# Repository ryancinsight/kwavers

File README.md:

# Kwavers 🌀

**An interdisciplinary ultrasound-light physics simulation library.** Kwavers models acoustic wave propagation, cavitation dynamics, and sonoluminescence for multi-modal imaging research and physics studies.

## 📋 Library Components

### Physics Models
- **Acoustic Wave Propagation**: Linear and nonlinear wave equations
- **Cavitation Dynamics**: Bubble physics implementations
- **Multi-Physics Coupling**: Basic acoustic-thermal interactions
- **Electromagnetic Models**: Wave propagation in various media

### Numerical Methods
- **FDTD Solver**: Finite difference time domain implementation
- **PSTD Solver**: Pseudospectral time domain method
- **PINN Support**: Physics-informed neural networks (experimental)
- **Boundary Conditions**: Various absorbing and reflecting boundaries

### Application Areas
- **Research Simulations**: Acoustic wave propagation studies
- **Imaging Algorithms**: Basic beamforming and reconstruction
- **Material Modeling**: Acoustic properties of different media
- **Signal Processing**: Filtering and analysis utilities

## 📊 Current Development Status

**Recently completed:** the workspace crate split (ADR-011) — the ~460k-LOC
`kwavers` monolith is decomposed into per-layer crates to cut incremental build
times. There is **no facade**: consumers (including the Python bindings) depend on
the layer crates directly (`kwavers_core`, `kwavers_grid`, `kwavers_solver`, …).
The `kwavers` crate is now only a thin top-level **app/integration** crate — it
hosts the binary and the cross-cutting tests/examples/benches, and re-exports
nothing.

### Workspace layout

| Crate | Layer / responsibility |
|-------|------------------------|
| [`kwavers-core`](crates/kwavers-core) | Constants, error types, arena allocation, time/logging utilities |
| [`kwavers-math`](crates/kwavers-math) | FFT, linear algebra, numerics, geometry, statistics, SIMD |
| [`kwavers-grid`](crates/kwavers-grid) | Cartesian/cylindrical grids, coordinates, topology, operators, geometric domains |
| [`kwavers-field`](crates/kwavers-field) | Field component indices (SSOT), field-type mapping, operations, statistics |
| [`kwavers-signal`](crates/kwavers-signal) | Waveforms, pulses, sweeps, modulation, windowing, filters |
| [`kwavers-medium`](crates/kwavers-medium) | Homogeneous/heterogeneous media, acoustic/elastic/optical/thermal properties |
| [`kwavers-phantom`](crates/kwavers-phantom) | Clinical tissue-phantom builders and Shepp-Logan references |
| [`kwavers-mesh`](crates/kwavers-mesh) | Tetrahedral FEM meshes, quality metrics, gaia bridge |
| [`kwavers-boundary`](crates/kwavers-boundary) | CPML/PML absorbing layers, FEM/BEM boundaries, coupling, periodic |
| [`kwavers-source`](crates/kwavers-source) | `Source` trait, grid/mask sources, wavefronts, apodization |
| [`kwavers-receiver`](crates/kwavers-receiver) | Sensor-array geometry (SSOT), recorders, point sensors, grid sampling |
| [`kwavers-transducer`](crates/kwavers-transducer) | Bowls, phased/linear/matrix/hemispherical arrays, beamforming, PAM, ultrafast |
| [`kwavers-imaging`](crates/kwavers-imaging) | DICOM/CT/NIfTI loaders, ultrasound/photoacoustic models, CEUS, fusion |
| [`kwavers-physics`](crates/kwavers-physics) | Nonlinear acoustics, bubble dynamics, thermal, optics, chemistry, elastic waves |
| [`kwavers-solver`](crates/kwavers-solver) | FDTD / PSTD / k-space / Helmholtz, BEM, FWI / RTM / CBS, PINN |
| [`kwavers-gpu`](crates/kwavers-gpu) | Hephaestus-backed provider-generic GPU backend; concrete `ComputeBackend` impls |
| [`kwavers-simulation`](crates/kwavers-simulation) | Builders, runners, multi-physics coupling, modality pipelines, backends |
| [`kwavers-analysis`](crates/kwavers-analysis) | Signal processing, conservation, validation, ML/uncertainty, plotting |
| [`kwavers-diagnostics`](crates/kwavers-diagnostics) | Reconstruction, multi-modal fusion, Doppler, spectroscopy, decision support |
| [`kwavers-therapy`](crates/kwavers-therapy) | HIFU / histotripsy / lithotripsy planning, theranostic guidance, dose & safety |
| [`kwavers-driver`](crates/kwavers-driver) | Physics-guided, manufacturing-aware driver-electronics (PCB) design |
| [`kwavers`](crates/kwavers) | Thin top-level app/integration crate: binary + cross-cutting tests/examples/benches (no re-exports) |
| [`kwavers-python`](crates/kwavers-python) | PyO3 bindings (`pykwavers`); depends on the layer crates directly; no domain logic |

Tyche owns reproducible counter streams, Latin-hypercube and Sobol designs,
online moments, correlation screening, and finite-sample conformal
calibration. Kwavers owns physical-domain transforms, model execution, Leto
array presentation, and domain-specific score definitions. Geometry maps
Tyche designs directly into validated rectangles, disks, and balls through one
single-allocation collector; Analysis and PINN fixed-design code carry no
independent provider algorithms, while model-residual adaptive refinement
remains solver-owned. See
[ADR 043](docs/ADR/043-tyche-uncertainty-provider.md).

Layer crates are at `3.0.0`; the completed split targets `4.0.0` (see
[RELEASE_v4.0.0 notes in CHANGELOG](CHANGELOG.md)). `kwavers-python` is `0.1.0`.

Validation status: the k-space pseudospectral solver matches the k-Wave
reference solver on the homogeneous-water IVP benchmark at Pearson
r = 1.000000000 (2-D) and r = 0.999999994 (3-D). The comparison is a Rust test in
the default gate against reference fields committed to this repository — see
[Reference Benchmark Coverage](#reference-benchmark-coverage).

### Python Releases

GitHub Releases tagged `kwavers-python-v<version>` build one locked
Python-3.8-compatible stable-ABI wheel per operating system for Linux, Windows,
and macOS. The workflow installs and imports each wheel as `pykwavers`, verifies
the `kwavers-python` distribution identity and Cargo-owned version, attests and
attaches the exact artifacts, then publishes that same wheel set to PyPI
through OIDC Trusted Publishing.

### Rust Crate Releases

The 23 reusable Rust packages publish to crates.io in local dependency order.
The `Crates.io Release` workflow validates a named workspace package on manual
dispatch. After its required first release is bootstrapped and its crates.io
Trusted Publisher is registered, a GitHub Release tagged
`crate-<package>-v<version>` packages, verifies, and publishes the matching
Cargo version with a short-lived OIDC token. Validation runs in a separate
read-only job. The publish job is bound to the GitHub `crates-io` environment.
The PyO3 and `xtask` packages are explicitly non-publishable; all Rust library
releases use their package names.

Detailed history lives in [`CHANGELOG.md`](CHANGELOG.md); current work and gaps
are tracked in [`backlog.md`](backlog.md), [`CHECKLIST.md`](CHECKLIST.md), and
[`gap_audit.md`](gap_audit.md).

### Architecture Overview

Kwavers follows a layered architecture designed for scientific computing:

```
Therapy / Diagnostics → Clinical planning, theranostic guidance, dose & safety
Simulation Layer      → Multi-physics orchestration, modality pipelines
Analysis Layer        → Signal processing, beamforming, imaging algorithms
Solver Layer          → Numerical methods (FDTD, PSTD, k-space, FWI, PINN)
Physics Layer         → Wave equations, bubble dynamics, constitutive relations
Domain Layer          → Problem geometry, materials, sources, sensors
Math Layer            → Linear algebra, FFT, numerical primitives
Core Layer            → Fundamental types, error handling
```

The module DAG is acyclic and linear (`core → math → domain → physics → solver →
analysis → simulation → diagnostics/therapy`); each layer is now its own crate.

Cross-repository foundations remain below that DAG. Public
[Asclepius](https://github.com/ryancinsight/asclepius) owns CEM43, Arrhenius
thermal damage, and independent-insult composition. Kwavers converts stored
temperatures to Aequitas quantities at its boundaries and retains spatial
fields, tissue presets, clinical thresholds, and an independent validation
oracle. See [ADR 044](docs/ADR/044-asclepius-response-ownership.md).

Public [Hyperion](https://github.com/ryancinsight/hyperion) owns photon and
optical interaction coefficients, reduced scattering, optical depth,
Beer-Lambert transmission, and the diffusion-derived coefficient laws.
`kwavers-medium` retains tissue identity, refractive index, presets, and maps;
`kwavers-physics` and `kwavers-solver` retain spatial transport algorithms and
photoacoustic coupling. This boundary removes the former `kwavers-optics`
formula module plus the parallel `DiffusionOpticalProperties` and
`OpticalAbsorption` models instead of adding a facade around them. See
[ADR 046](docs/ADR/046-hyperion-optical-transport-ownership.md).

Key architectural decisions:
- **Layer Separation**: Unidirectional dependencies prevent circular imports
- **Domain Purity**: Core entities remain free of application logic
- **Trait-Based Design**: Physics specifications defined as traits for testability
- **Feature Flags**: Optional components (GPU, PINN, API) can be enabled as needed

## 🚀 Quick Start

### Installation

Add the layer crates you need to your `Cargo.toml`:

```toml
[dependencies]
kwavers-grid = "3.0.0"
kwavers-medium = "4.0.0"
```

For GPU acceleration and advanced features, add the top-level integration crate:

```toml
[dependencies]
kwavers = { version = "3.0.0", features = ["gpu", "pinn"] }
```

### Example 1: Basic Grid Setup

```rust
use kwavers_grid::Grid;

fn main() -> Result<(), Box<dyn std::error::Error>> {
    // Create a 3D computational grid
    let grid = Grid::new(100, 100, 100, 0.001, 0.001, 0.001)?;
    println!("Created grid: {}×{}×{} points", grid.nx, grid.ny, grid.nz);
    println!("Grid spacing: {} m", grid.dx);
    Ok(())
}
```

### Example 2: Material Properties

```rust
use kwavers_grid::Grid;
use kwavers_medium::HomogeneousMedium;

fn main() -> Result<(), Box<dyn std::error::Error>> {
    // Create a computational grid
    let grid = Grid::new(100, 100, 100, 0.001, 0.001, 0.001)?;

    // Define acoustic properties for water
    let density = 1000.0;      // kg/m³
    let sound_speed = 1500.0;  // m/s
    let mu_a = 0.0;            // optical absorption coefficient (1/m)
    let mu_s_prime = 0.0;      // reduced optical scattering coefficient (1/m)

    // Create a homogeneous water medium
    let medium = HomogeneousMedium::new(
        density,
        sound_speed,
        mu_a,
        mu_s_prime,
        &grid,
    );

    println!("Water properties:");
    println!("  Density: {} kg/m³", density);
    println!("  Sound speed: {} m/s", sound_speed);
    println!("  Acoustic impedance: {} MPa·s/m", density * sound_speed / 1e6);

    Ok(())
}
```

### Example 3: Basic Acoustic Calculations

```rust
// Basic acoustic property calculations
fn main() {
    // Acoustic impedance calculation: Z = ρc
    let density_water = 1000.0;     // kg/m³
    let speed_water = 1500.0;       // m/s
    let impedance_water = density_water * speed_water; // Pa·s/m

    println!("Water acoustic impedance: {:.0} Pa·s/m", impedance_water);

    // Reflection coefficient: R = (Z2 - Z1)/(Z2 + Z1)
    let density_air = 1.2;          // kg/m³
    let speed_air = 343.0;          // m/s
    let impedance_air = density_air * speed_air;

    let reflection_coeff = (impedance_air - impedance_water) /
                          (impedance_air + impedance_water);

    println!("Air-water reflection coefficient: {:.4}", reflection_coeff);
}
```

## 📚 Documentation

### 📖 Documentation

- **[Published Kwavers book](https://ryancinsight.github.io/kwavers/)** - Hosted mdBook site
- **[API Reference](https://docs.rs/kwavers)** - Generated Rust documentation
- **[Examples](examples/)** - Basic usage examples
- **[The Kwavers book](docs/book/)** - Chapters, figures, validation narratives
- **[Architecture Decision Records](docs/ADR/)** - Design decisions (incl. ADR-011 crate split)
- **[Documentation index](docs/README.md)** - What lives under `docs/`

### 🎯 Basic Usage

See the `examples/` directory for basic usage patterns:

```bash
# List available examples
cargo run --example

# Run a basic example (if available)
cargo run --example basic_simulation
```

**Basic Test**: Check compilation
```bash
cargo check
```

### 🏗️ Architecture

Kwavers is structured with layered separation intended to support scientific computing workflows:

```
Clinical Applications    → Research use cases, safety monitoring
Analysis & Imaging       → Signal processing, reconstruction algorithms
Simulation Orchestration → Multi-physics coupling, time integration
Numerical Solvers        → FDTD, PSTD, PINN, spectral methods
Physics Specifications   → Wave equations, constitutive relations
Problem Domain           → Geometry, materials, boundary conditions
Mathematical Primitives  → Linear algebra, FFT, interpolation
Core Infrastructure      → Error handling, memory management
```

The architecture aims to separate concerns while maintaining flexibility for different research applications. Layer boundaries help organize code but are not strictly enforced in all areas during active development.

## 🤝 Contributing

This is an active research project under development. Contributions are welcome! The codebase follows strict quality standards and clean architecture principles.

### 📝 Development Philosophy

- **Clean Codebase**: No dead code, deprecated code, or build artifacts
- **Deep Vertical Hierarchy**: Modules organized by domain with clear separation of concerns
- **Single Source of Truth**: Shared accessors, no duplication
- **Zero Technical Debt**: All TODOs resolved with full implementation or removed
- **Architectural Purity**: Unidirectional dependencies, no circular imports

### 🚀 Getting Started

1. **Check Status**: Review [`CHECKLIST.md`](CHECKLIST.md) for current task status
2. **Review Plans**: See [`backlog.md`](backlog.md) for planned work and [`gap_audit.md`](gap_audit.md) for known gaps
3. **Build a crate**: `cargo check -p kwavers-core` (per-crate checks are fast post-split)
4. **Run Tests**: `cargo nextest run -p <crate>`; use
   `cargo test-gpu-consumers` when changing the shared GPU simulation/Python
   dependency graph, so Cargo compiles their common graph once; use
   `cargo test -p <crate> --doc` for doctests
5. **Read Docs**: [`docs/book/`](docs/book/) for narratives, [`docs/ADR/`](docs/ADR/) for design decisions
6. **Install the hooks**: `git config core.hooksPath .githooks`

   Git never applies tracked hooks on its own, so this is a one-time step per
   clone. The `pre-push` hook runs `scripts/lockfile.py --check`, which is the
   same check CI runs. It matters most when working inside the Atlas stack: the
   stack's `[patch]` overlay makes cargo resolve first-party dependencies to
   local paths and write a `Cargo.lock` with every `source = "git+..."` line
   stripped. That lock resolves fine under the overlay and fails every
   `--locked` job in CI, so without the hook the corruption is invisible until a
   runner reports it. Repair with `python3 scripts/lockfile.py --regenerate`.

### 📊 Development Approach

**Artifact-driven sprints** (see [`CLAUDE.md`](CLAUDE.md) governance):
- `backlog.md` — strategy and prioritized work
- `CHECKLIST.md` — tactical tasks with change-class tags
- `gap_audit.md` — physics/numerics gap findings
- `CHANGELOG.md` — version history

**Quality Standards**:
- Zero compilation errors (enforced)
- Minimal compiler warnings (dead code not allowed)
- 100% test pass rate for all refactoring
- API compatibility maintained across refactors
- Mathematical specifications with literature references

### 🔬 Research Integration

Kwavers is being enhanced with methods from leading ultrasound simulation projects:
- **k-Wave** (MATLAB): k-space pseudospectral methods, advanced source modeling
- **jwave** (JAX/Python): Differentiable simulations, GPU parallelization
- **k-wave-python**: Python binding patterns, HDF5 standards
- **KWave.jl** (Julia): MATLAB-free k-Wave implementation for 1-D/2-D/3-D reference benchmarking
- **optimus**: Optimization frameworks, inverse problems
- **fullwave25**: Full-wave simulation, clinical workflows
- **dbua**: Neural beamforming, real-time inference
- **simsonic**: Advanced tissue models, multi-modal integration

### 📊 History

Per-version history is consolidated in [`CHANGELOG.md`](CHANGELOG.md). The
historical per-sprint/per-phase reports formerly under `docs/` were pruned
during the workspace-split docs cleanup and remain recoverable from git history.

## 📄 License

Kwavers is licensed under the **MIT License**. See [LICENSE](LICENSE) for details.

## 📚 References

### Key Physics Texts
- Hamilton, M.F. & Blackstock, D.T. - Nonlinear Acoustics
- Szabo, T.L. - Diagnostic Ultrasound Imaging
- Duck, F.A. - Physical Properties of Tissues

### Numerical Methods
- Yee, K.S. (1966) - FDTD method
- Liu, Q.H. (1997) - PSTD method
- Hesthaven, J.S. (2007) - DG methods

### Related Simulation Projects
- **k-Wave**: MATLAB toolbox for acoustic wave simulation ([GitHub](https://github.com/ucl-bug/k-wave))
- **jwave**: JAX-based differentiable acoustic simulations ([GitHub](https://github.com/ucl-bug/jwave))
- **k-wave-python**: Python interface to k-Wave ([GitHub](https://github.com/waltsims/k-wave-python))
- **KWave.jl**: Julia implementation of k-Wave for MATLAB-free acoustic simulation benchmarks ([GitHub](https://github.com/JClingo/k-wave-julia))
- **optimus**: Optimization framework for ultrasound ([GitHub](https://github.com/optimuslib/optimus))
- **fullwave25**: Full-wave ultrasound simulator ([GitHub](https://github.com/pinton-lab/fullwave25))
- **dbua**: Deep learning beamforming ([GitHub](https://github.com/waltsims/dbua))
- **simsonic**: Advanced ultrasound simulation platform ([Website](https://www.simsonic.fr))

### Reference Benchmark Coverage

`crates/kwavers/tests/kwave_reference_parity.rs` compares the k-space
pseudospectral solver against k-Wave on the homogeneous-water IVP Gaussian case.
The reference fields live in `crates/kwavers/tests/reference/kwave/` (156 KB), so
the test runs from a clean clone in the default gate with no external solver
present. `scripts/generate_kwave_reference.py` regenerates them by driving
`k-wave-python` over the reference `kspaceFirstOrder-OMP` binary.

Both codes run the same grid, time step, step count, and Treeby-Cox k-space
correction, and are compared over a centred window the wavefront has entered but
neither code's boundary treatment has reached.

| Case | Grid | Steps | Relative L2 | Relative L-inf | Pearson r |
|------|------|-------|-------------|----------------|-----------|
| `ivp_homogeneous_2d` | 64 × 64 | 100 | 5.50e-7 | 1.05e-6 | 1.000000000 |
| `ivp_homogeneous_3d` | 32 × 32 × 32 | 50 | 1.06e-4 | 2.20e-4 | 0.999999994 |
| `ivp_absorbing_2d` | 64 × 64 | 100 | 8.10e-3 | 4.99e-3 | 0.999999924 |
| `ivp_layered_2d` | 80 × 64 | 120 | 7.97e-3 | 1.54e-2 | 0.999963422 |
| `src_tone_burst_2d` | 96 × 80 | 151 | 2.58e-3 | 2.20e-3 | 0.999996674 |
| `src_nonlinear_2d` | 96 × 80 | 151 | 3.30e-3 | 2.80e-3 | 0.999994550 |

The finite-difference solver is measured against the same reference as a
cross-scheme check, since the pseudospectral solver shares its k-space machinery
and cannot be an independent oracle for it. It separates by `2.53e-2` relative
L2 at `r = 0.999647`, which is its own fourth-order dispersion error and is
gated as such rather than at the pseudospectral bound.

`ivp_absorbing_2d` is the lossless 2-D case with power-law absorption
(`40 dB/(MHz^1.5 cm)`, `y = 1.5`) and nothing else changed, so the pair isolates
the absorption model; the test asserts both that kwavers matches the absorbing
reference and that the absorbing field separates from the lossless one, since
agreement alone would not prove the model ran.

`ivp_layered_2d` steps sound speed and density across a smoothed interface eight
cells from the seed, so the recorded field carries a transmitted wave, a
reflection, and a refracted front; it is measured against a uniform-medium run at
the same discretization, which it separates from by `0.27`. Its grid is
deliberately non-square — a square case cannot distinguish a correct axis
orientation from a transposed one, and two such conventions were live in the
harness until this case exposed them.

`src_tone_burst_2d` drives a Gaussian-windowed 3 MHz burst from a single
off-centre cell, starting from a zero field. It is the only case that reaches
the source injection path, and it checks four conventions at once: the mask's
cell lookup, the per-step signal indexing, k-Wave's source-term scaling, and the
k-space source correction.

`src_nonlinear_2d` is that case with finite-amplitude propagation switched on
(`B/A = 20` at 5 MPa), sized to reach roughly seventy percent of the plane-wave
shock distance — as far into the nonlinear regime as the smooth-wave assumption
reaches, since neither code has shock capturing. It separates from a linear run
by `4.58e-2`, fourteen times its own residual.

`k-wave-python` ships no 1-D solver, so there is no 1-D row; the axisymmetric
case is a separate geometry and is not yet covered. Elastic propagation and
distributed (multi-cell) sources have no committed reference field yet and are
not covered by this result.
[ADR 119](docs/adr/119-kwave-reference-oracle.md) records the reference
provenance, the tolerance derivation, and what the comparison does not establish.

### Key Publications
1. Treeby & Cox (2010) - "k-Wave: MATLAB toolbox for photoacoustic simulation" - J. Biomed. Opt. 15(2), 021314
2. Treeby et al. (2012) - "Nonlinear ultrasound propagation in heterogeneous media" - J. Acoust. Soc. Am. 131(6), 4324-4336
3. Wise et al. (2019) - "Arbitrary acoustic source distributions" - J. Acoust. Soc. Am. 146(1), 278-288
4. Treeby et al. (2020) - "Axisymmetric k-space method" - J. Acoust. Soc. Am. 148(4), 2288-2300

## 📞 Contact & Support

- **Issues**: [GitHub Issues](https://github.com/kwavers/kwavers/issues)
- **Discussions**: [GitHub Discussions](https://github.com/kwavers/kwavers/discussions)
- **Documentation**: [docs.rs/kwavers](https://docs.rs/kwavers)

---

**A research library for acoustic and optical physics simulations.**

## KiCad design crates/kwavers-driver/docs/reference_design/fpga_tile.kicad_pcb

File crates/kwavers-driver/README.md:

# kwavers-driver

Physics-guided, manufacturing-aware driver-electronics design for
[kwavers](https://github.com/ryancinsight/kwavers).

The crate designs the high-voltage ultrasound driver boards that feed a kwavers transducer
model: it places components under a physics and DFM objective, routes them with a
negotiated-congestion router, verifies the result against fabrication and electrical rules,
and emits a deterministic artifact set that ties the generated board back to
[`kwavers-transducer`](https://docs.rs/kwavers-transducer)'s beam-propagation pipeline.

## Why not a sequential A\* router

A maze router commits each net greedily, so early nets wall off later ones. In a congested
region — a shared SPI daisy-chain, a BGA escape, a high-voltage fan-in — no mechanism lets
one net step aside for a more constrained one, and the solution becomes order-dependent:
on the dense multi-channel tiles it does not converge. The geometry is the wall, not the
effort.

## The algorithm

`route` implements **negotiated-congestion routing** (PathFinder — McMurchie & Ebeling,
*FPGA '95*). Every net routes every iteration, temporary overlap allowed; a node's cost is

```text
cost(n) = (base(n) + history(n)) * (1 + overuse(n) * present_factor)
```

`present_factor` escalates each iteration and `history(n)` accumulates on persistently
overused nodes, so nets *negotiate* shared resources until the routing is **legal** — no
node over capacity. This is order-independent, the property A\* lacks.

Multi-terminal nets grow as trees, not as pairwise connections, and the growth strategy is
chosen by net class: power and ground expand Prim-style from any terminal, while signal and
high-voltage nets use chain-tip growth — the search source moves to each reached terminal —
so a multi-terminal high-speed net forms a daisy chain (degree ≤ 2) instead of branching
stubs.

## Physics guidance

`cost::RoutingCost` is the extension seam: `base(n)` folds the physics and manufacturing
constraints into the search instead of checking them after the fact. `cost::PhysicsCost`
implements

- **high-voltage creepage** as a spatial hazard gradient — an HV net pays a rising cost as
  it approaches low-voltage features, and vice versa, so the clearance rule *shapes* the
  route instead of failing DRC afterwards; and
- **layer affinity** — HV to outer copper, since creepage is a surface phenomenon; control
  to inner copper, shielded between planes.

A thermal- or impedance-aware cost is a new `impl RoutingCost`, not a router change.

## Public surface

`use kwavers_driver::prelude::*;` brings the unit newtypes, geometry, board model, and
physics facade into scope.

| Module | Responsibility |
|---|---|
| `units` | Unit newtypes (`Nm`, `Hz`, `Ohm`, `Volt`, `Amp`, `Watt`, `Kelvin`, …) — type-level unit safety at zero runtime cost |
| `geom` | Exact nanometre geometry (`Nm`, `Point`) and the `GridSpec` lattice |
| `board` | Pure domain model: nets, pads, tracks, vias, `NetClassKind`, split domains |
| `rules` | `DesignRules` (fabrication floors) and the high-voltage creepage rule |
| `cost` | `RoutingCost` seam and `PhysicsCost` |
| `route` | Grid resource model, multi-source search, the PathFinder loop, copper emission |
| `place` | Physics/DFM simulated-annealing placer (rotation, congestion and weakness feedback) |
| `pipeline` | Place→route bridge and the place↔route co-optimization loop |
| `dfm` | Post-routing manufacturability: teardrops, mitring, via dedup, ampacity widening, ground pour |
| `optim` | Joint driver–thermal–acoustic co-optimization |
| `verify` | ERC, DRC, LVS, assembly, keep-in, BOM, isolation BFS, AC coupling — `verify_all` |
| `audit` | Adversarial DFM/SI critic: crossings, clearance, near-short risk, crosstalk, via adjacency, antenna |
| `fabrication` | Fabrication-readiness verification |
| `component_db` / `component_accuracy` | Sourced part database and CAD/footprint accuracy manifest |
| `driver` | Driver power loss, efficiency, and matching-network physics |
| `five_level` / `pulse_skip` / `tr_switch` | Pulser topology, adaptive pulse skipping, T/R switch models |
| `stack` | Multi-tile stack planning: board count, channels per board, connector and thermal compatibility |
| `manifest` | Driver-to-simulation manifest — the handoff to the acoustic pipeline |
| `validate` | Whole-design physics validation across the per-domain models |
| `experiment` | End-to-end driver + transducer experiment orchestration (`run_experiment`, `build_beam_report`) |
| `render` | Native SVG renderer for the routed board |
| `io` / `kicad_cli` | KiCad file emission and the external `kicad-cli` wrapper (feature `io`) |
| `error` | Per-slice error hierarchy |
| `ssot` | Cross-cutting constants and string literals |

## Physics and analysis suite

Each axis under `physics` is a standard or first-principles model with a value-semantic
test — an analytical oracle, a published reference point, or an independent cross-check —
and feeds the adversarial place↔route loop where it informs the layout.

| Slice | Physics |
|---|---|
| `physics::thermal` | 2-D heat conduction (validated against a manufactured solution) · electro-thermal Joule coupling · thermal vias · transient τ |
| `physics::ampacity` | IPC-2221 width and resistance · skin depth / AC resistance · current density · electromigration (Black) · plated-through-hole aspect ratio |
| `physics::emi` | Commutation-loop inductance · trace inductance · capacitive drive current · L·dI/dt overshoot · switching, gate, and recovery loss |
| `physics::pdn` | IR drop (Gauss–Seidel resistor network) · target impedance · hold-up capacitance · decoupling SRF |
| `physics::dielectric` | Paschen air breakdown · IPC-2221 voltage spacing · CAF time-to-failure |
| `physics::si` | Microstrip impedance · propagation delay · skew budget |
| `physics::acoustic` | Wavelength · grating-lobe steering · BVD resonance · near-field / f-number · element directivity · tissue attenuation |

Cross-checks fall out of the models rather than being asserted into them: the BVD series
resonance of the modeled element lands on the drive frequency
(`bvd_resonance_matches_2mhz_drive`), and the commutation-loop model reproduces the
pulser's rated peak drive current from its loop inductance and node capacitance.

## Evidence tier

Negotiated-congestion convergence (legality on a congested instance with no single-layer
solution) and the creepage-gradient effect are covered by value-semantic unit tests in
their modules — property and empirical tier, not a machine-checked proof. The thermal
solver is verified against a manufactured solution at its stated order of accuracy.

## Status

`cargo nextest run -p kwavers-driver` runs **494 tests, all passing**, with `cargo fmt`
and Clippy clean.

The crate is the product of a phased refactor from `kicad-routing` (see
`docs/MIGRATION.md` and `docs/ARCHITECTURE.md`). Phases 0–5 have landed: the unit
newtypes, prelude, per-slice error hierarchy, geometry, cost, route, place, physics, and
output slices are migrated, and the `experiment` subtree orchestrates end-to-end driver +
transducer runs. **Phase 6 remains** — public-API examples and a docs backfill.

There is no `examples/` directory in this repository: the original per-tile and stack
example programs carry proprietary board geometry and are excluded from version control
(see the repository `.gitignore`). Phase 6 adds public-surface examples that exercise the
library without that geometry. Until then the library API and its tests are the executable
documentation.

## Build

```sh
cargo nextest run -p kwavers-driver
cargo clippy -p kwavers-driver --all-targets -- -D warnings
cargo doc -p kwavers-driver --no-deps
```

## Features

- `io` (default) — KiCad `.kicad_pcb` / `.kicad_dru` emission and the `kicad-cli` wrapper.
- `kwavers` — enables `experiment::KwaversSim`, the real acoustic simulator backed by
  `kwavers-transducer`. Without it, `experiment` uses the in-crate fallback simulator.

## Documentation

- API reference: <https://docs.rs/kwavers-driver>
- Architecture and refactor plan: `docs/ARCHITECTURE.md`, `docs/MIGRATION.md`
- Workspace overview and crate map: [kwavers README](https://github.com/ryancinsight/kwavers#readme)

## License

MIT

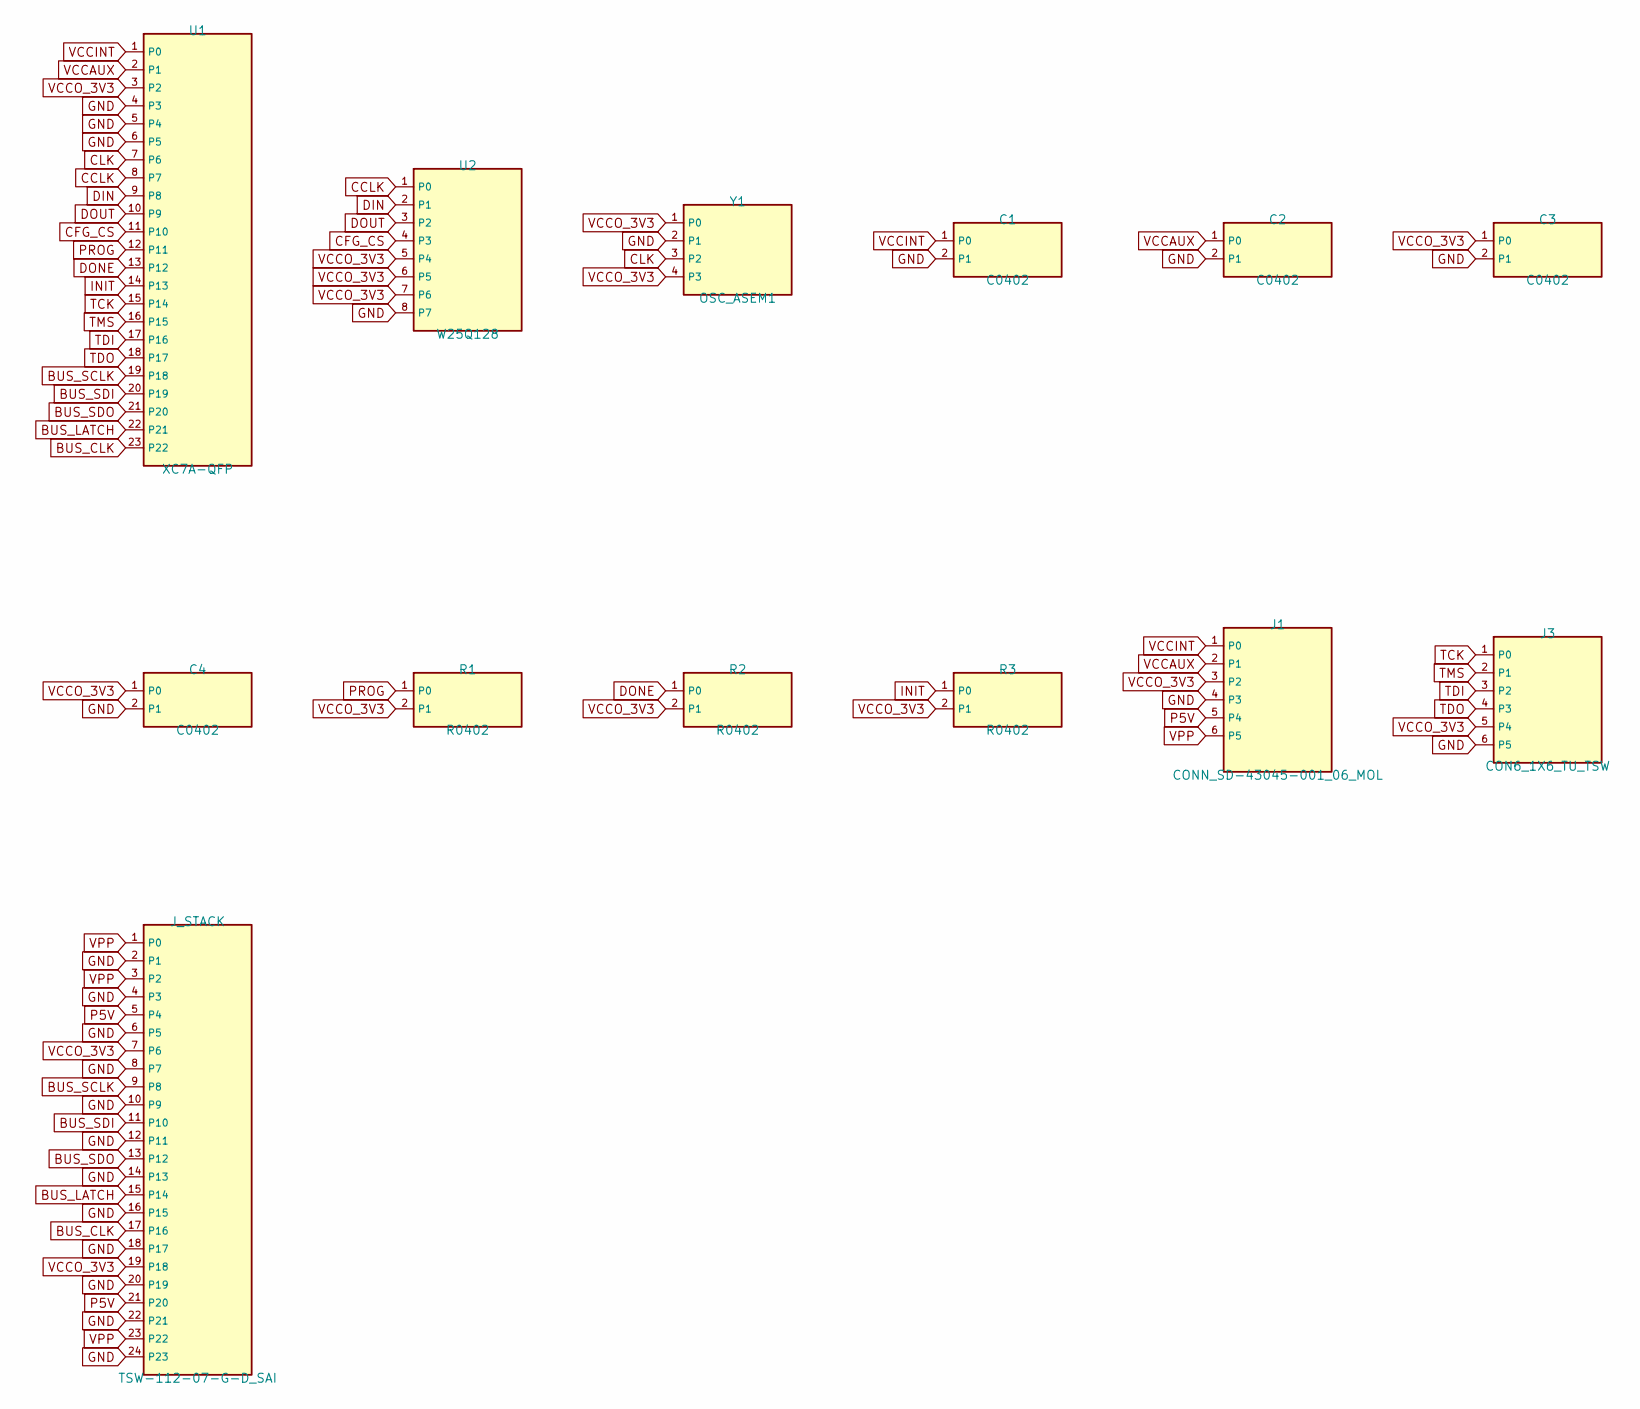
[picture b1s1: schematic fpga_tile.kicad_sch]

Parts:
C1, C2, C3, C4: C0402
J1: CONN_SD-43045-001_06_MOL
J3: CON6_1X6_TU_TSW
J_STACK: TSW-112-07-G-D_SAI
R1, R2, R3: R0402
U1: XC7A-QFP
U2: W25Q128
Y1: OSC_ASEM1

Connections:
BUS_CLK: J_STACK.17 (P16), U1.23 (P22)
BUS_LATCH: J_STACK.15 (P14), U1.22 (P21)
BUS_SCLK: J_STACK.9 (P8), U1.19 (P18)
BUS_SDI: J_STACK.11 (P10), U1.20 (P19)
BUS_SDO: J_STACK.13 (P12), U1.21 (P20)
CCLK: U1.8 (P7), U2.1 (P0)
CFG_CS: U1.11 (P10), U2.4 (P3)
CLK: U1.7 (P6), Y1.3 (P2)
DIN: U1.9 (P8), U2.2 (P1)
DONE: R2.1 (P0), U1.13 (P12)
DOUT: U1.10 (P9), U2.3 (P2)
GND: C1.2 (P1), C2.2 (P1), C3.2 (P1), C4.2 (P1), J1.4 (P3), J3.6 (P5), J_STACK.2 (P1), J_STACK.4 (P3), J_STACK.6 (P5), J_STACK.8 (P7), J_STACK.10 (P9), J_STACK.12 (P11), J_STACK.14 (P13), J_STACK.16 (P15), J_STACK.18 (P17), J_STACK.20 (P19), J_STACK.22 (P21), J_STACK.24 (P23), U1.4 (P3), U1.5 (P4), U1.6 (P5), U2.8 (P7), Y1.2 (P1)
INIT: R3.1 (P0), U1.14 (P13)
P5V: J1.5 (P4), J_STACK.5 (P4), J_STACK.21 (P20)
PROG: R1.1 (P0), U1.12 (P11)
TCK: J3.1 (P0), U1.15 (P14)
TDI: J3.3 (P2), U1.17 (P16)
TDO: J3.4 (P3), U1.18 (P17)
TMS: J3.2 (P1), U1.16 (P15)
VCCAUX: C2.1 (P0), J1.2 (P1), U1.2 (P1)
VCCINT: C1.1 (P0), J1.1 (P0), U1.1 (P0)
VCCO_3V3: C3.1 (P0), C4.1 (P0), J1.3 (P2), J3.5 (P4), J_STACK.7 (P6), J_STACK.19 (P18), R1.2 (P1), R2.2 (P1), R3.2 (P1), U1.3 (P2), U2.5 (P4), U2.6 (P5), U2.7 (P6), Y1.1 (P0), Y1.4 (P3)
VPP: J1.6 (P5), J_STACK.1 (P0), J_STACK.3 (P2), J_STACK.23 (P22)

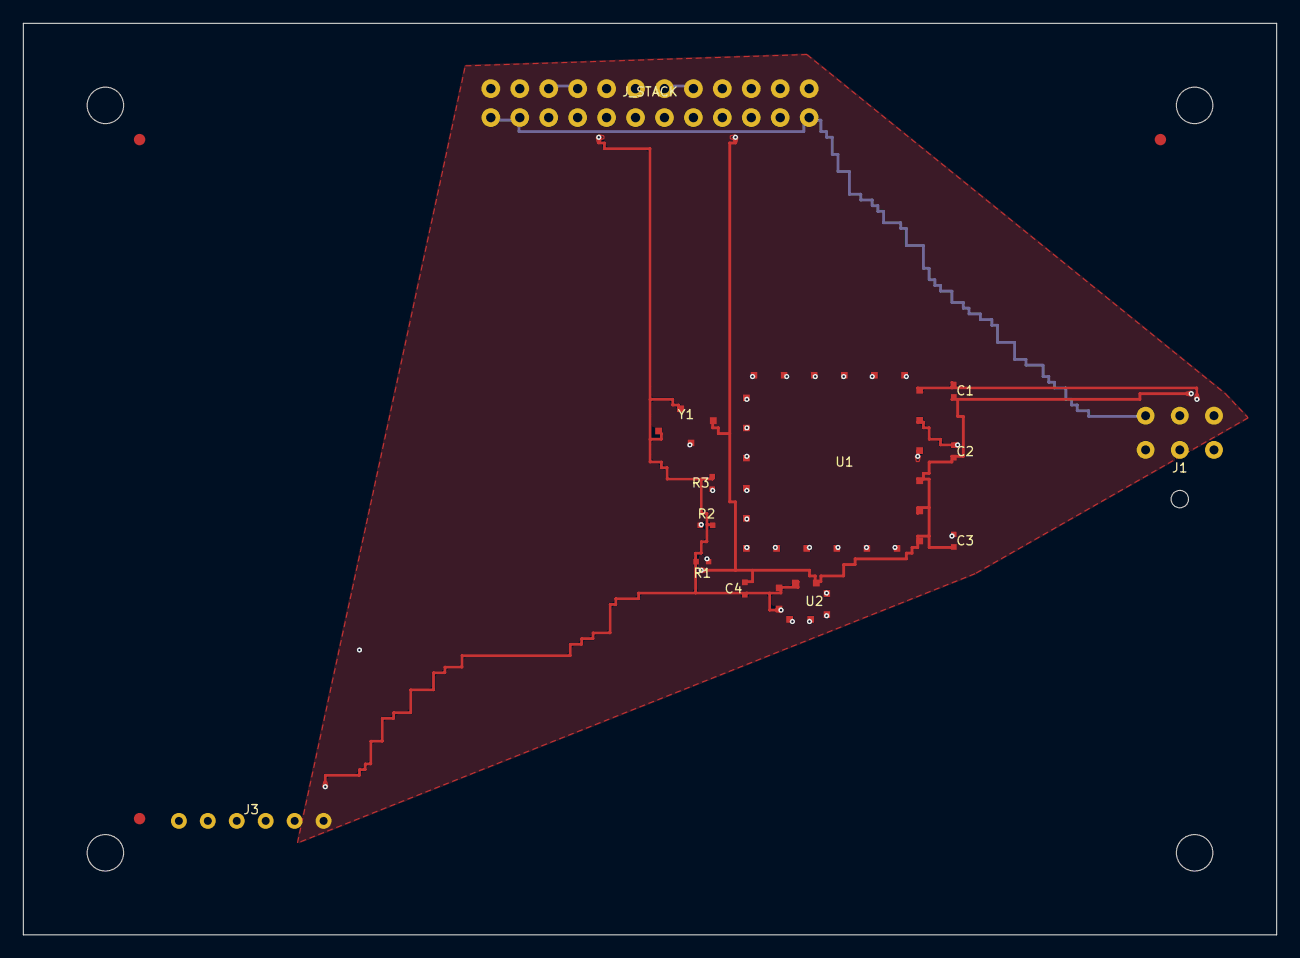
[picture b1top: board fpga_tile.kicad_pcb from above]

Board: 4 copper layers, 110.0 x 80.0 mm, 20 parts (0 on the bottom side), 23 nets.

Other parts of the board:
FID: FIDUCIAL
FID#2, FID#3: FIDUCIAL
MH: MountingHole
MH#2, MH#3, MH#4: MountingHole

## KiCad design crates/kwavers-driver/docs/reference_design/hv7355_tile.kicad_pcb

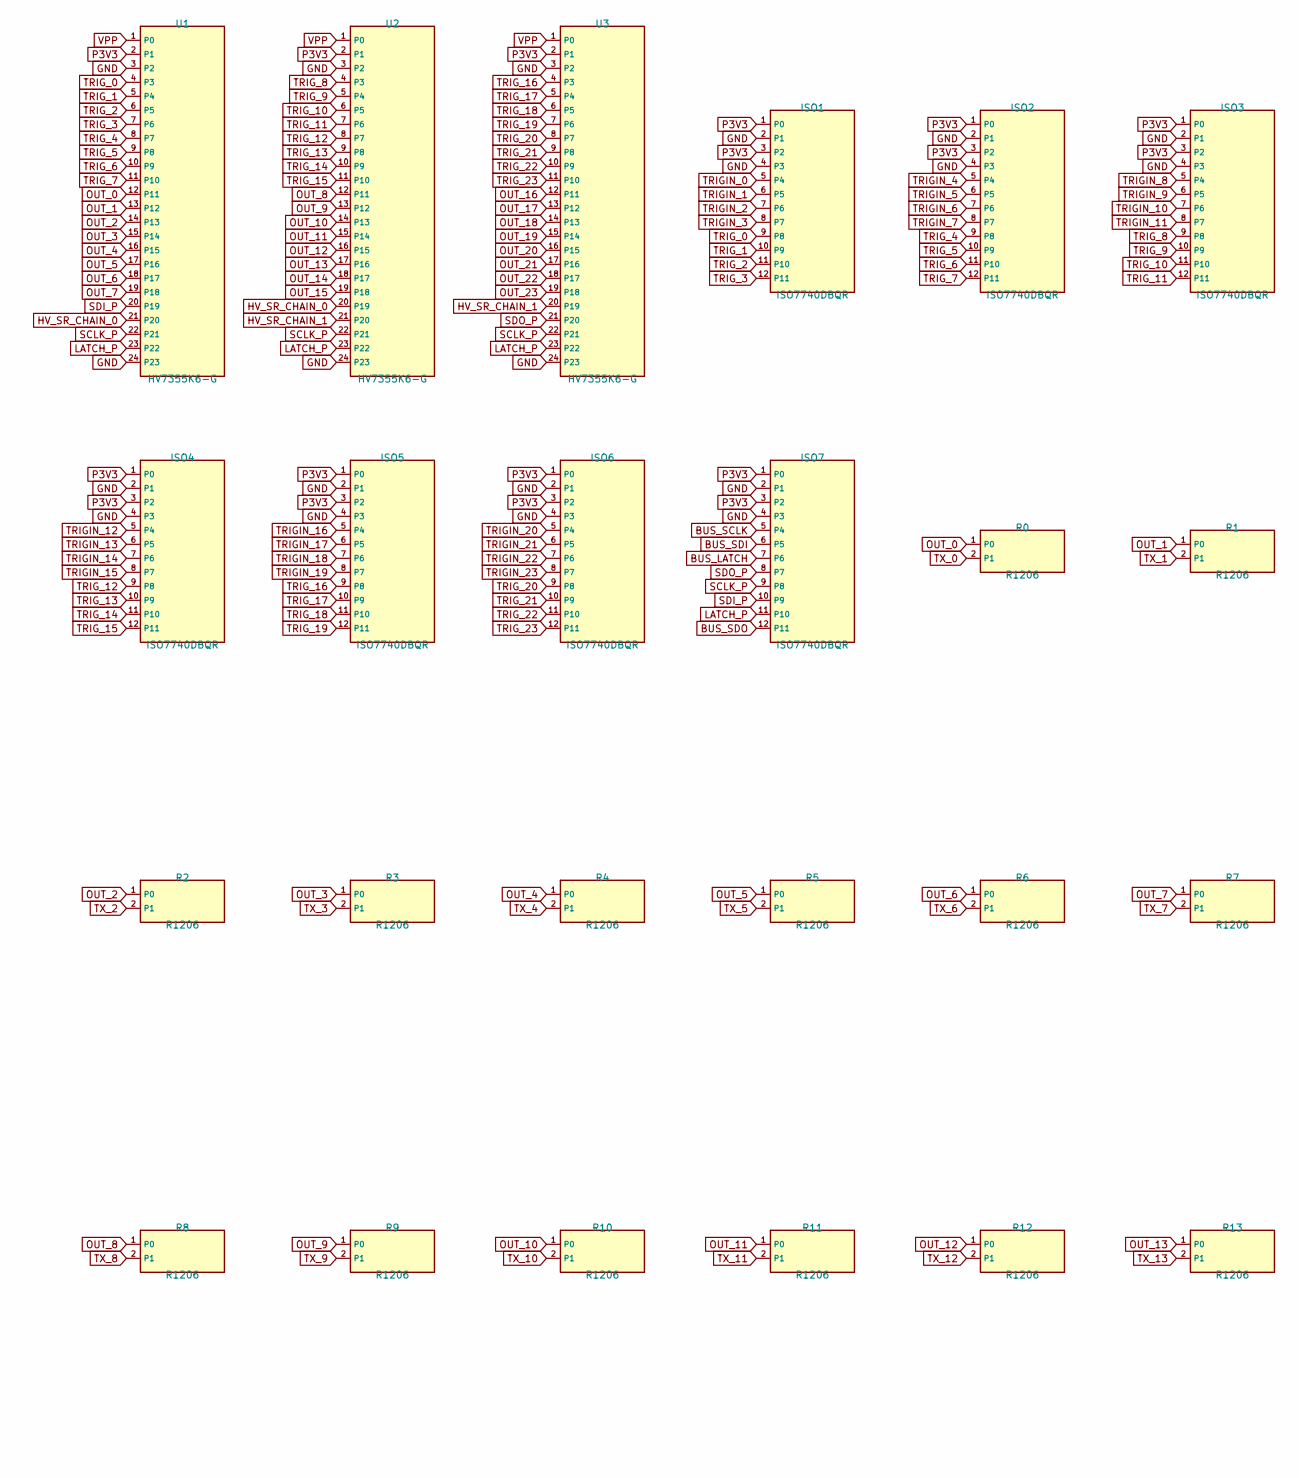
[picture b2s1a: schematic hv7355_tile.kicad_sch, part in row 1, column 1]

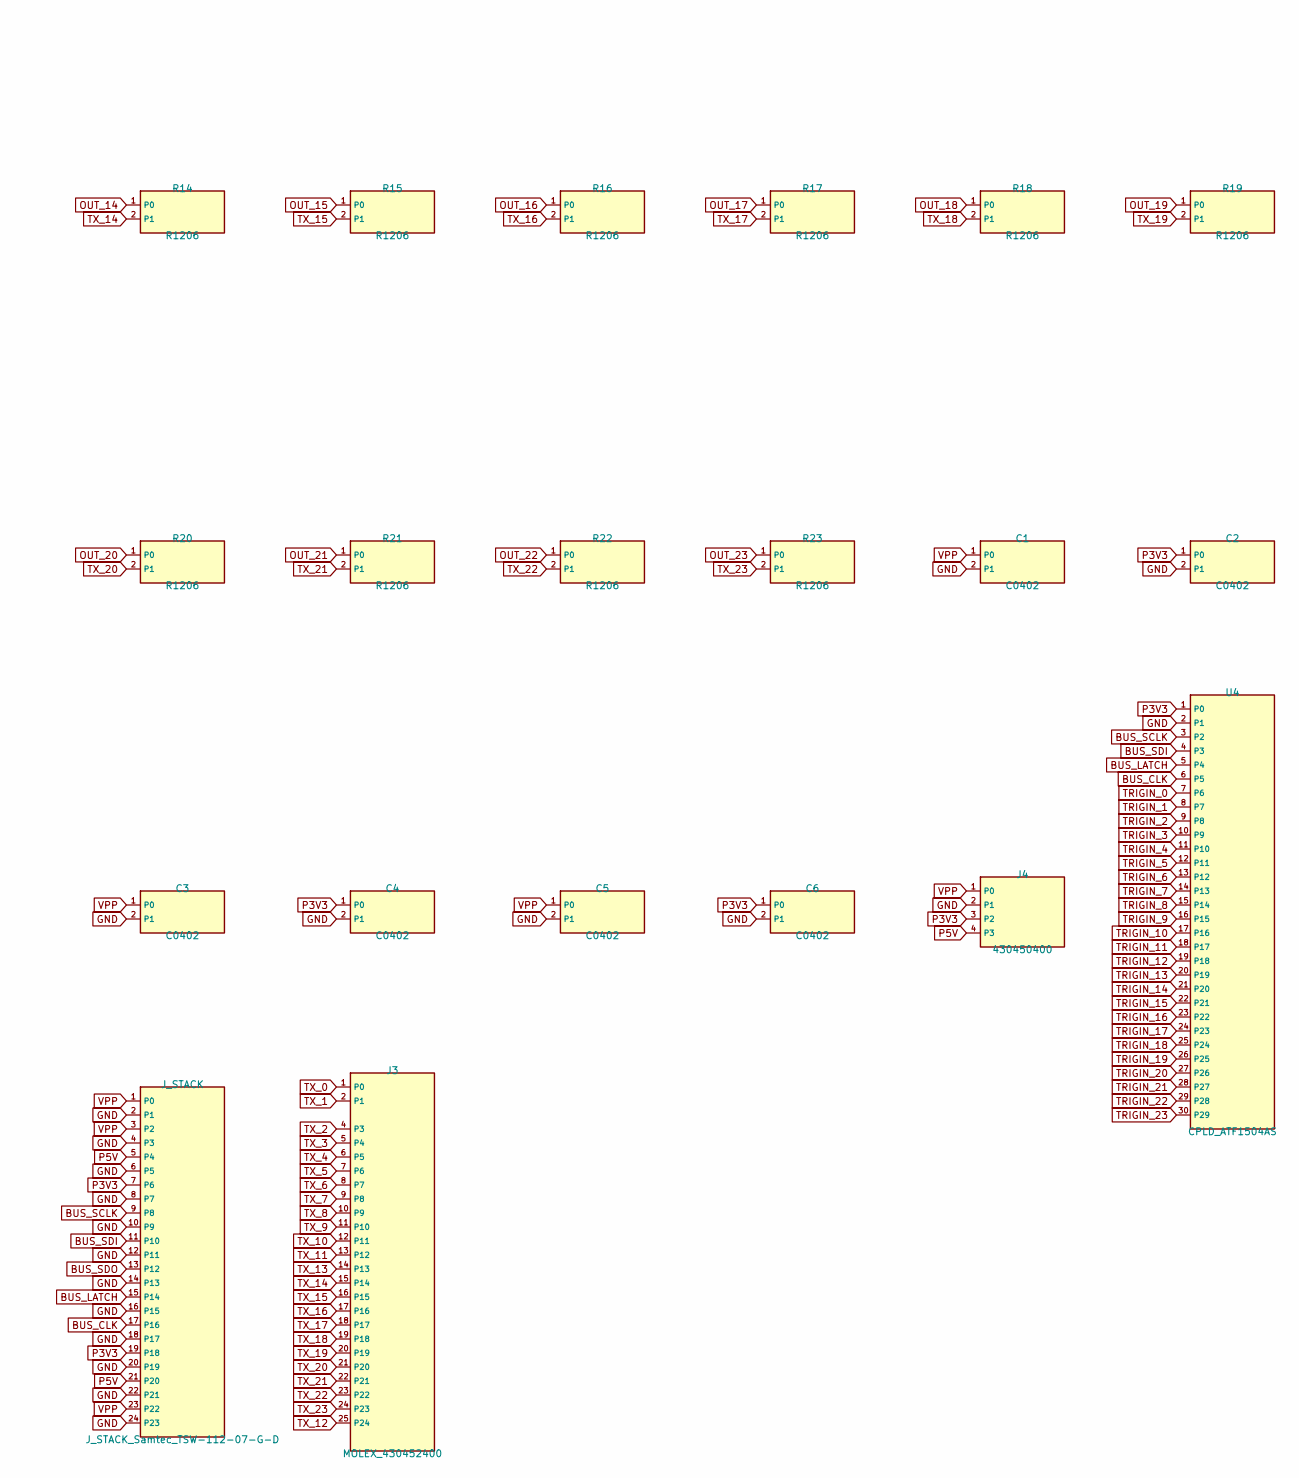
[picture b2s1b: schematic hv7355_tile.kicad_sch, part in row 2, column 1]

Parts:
C1, C2, C3, C4, C5, C6: C0402
ISO1, ISO2, ISO3, ISO4, ISO5, ISO6, ISO7: ISO7740DBQR
J3: MOLEX_430452400
J4: 430450400
J_STACK: J_STACK_Samtec_TSW-112-07-G-D
R0, R1, R2, R3, R4, R5, R6, R7, R8, R9, R10, R11, R12, R13, R14, R15, R16, R17, R18, R19, R20, R21, R22, R23: R1206
U1, U2, U3: HV7355K6-G
U4: CPLD_ATF1504AS

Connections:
BUS_CLK: J_STACK.17 (P16), U4.6 (P5); also elsewhere on the board
BUS_LATCH: ISO7.7 (P6), J_STACK.15 (P14), U4.5 (P4); also elsewhere on the board
BUS_SCLK: ISO7.5 (P4), J_STACK.9 (P8), U4.3 (P2); also elsewhere on the board
BUS_SDI: ISO7.6 (P5), J_STACK.11 (P10), U4.4 (P3); also elsewhere on the board
BUS_SDO: ISO7.12 (P11), J_STACK.13 (P12); also elsewhere on the board
GND: C1.2 (P1), C2.2 (P1), C3.2 (P1), C4.2 (P1), C5.2 (P1), C6.2 (P1), ISO1.2 (P1), ISO1.4 (P3), ISO2.2 (P1), ISO2.4 (P3), ISO3.2 (P1), ISO3.4 (P3), ISO4.2 (P1), ISO4.4 (P3), ISO5.2 (P1), ISO5.4 (P3), ISO6.2 (P1), ISO6.4 (P3), ISO7.2 (P1), ISO7.4 (P3), J4.2 (P1), J_STACK.2 (P1), J_STACK.4 (P3), J_STACK.6 (P5), J_STACK.8 (P7), J_STACK.10 (P9), J_STACK.12 (P11), J_STACK.14 (P13), J_STACK.16 (P15), J_STACK.18 (P17), J_STACK.20 (P19), J_STACK.22 (P21), J_STACK.24 (P23), U1.3 (P2), U1.24 (P23), U2.3 (P2), U2.24 (P23), U3.3 (P2), U3.24 (P23), U4.2 (P1); also elsewhere on the board
HV_SR_CHAIN_0: U1.21 (P20), U2.20 (P19)
HV_SR_CHAIN_1: U2.21 (P20), U3.20 (P19)
LATCH_P: ISO7.11 (P10), U1.23 (P22), U2.23 (P22), U3.23 (P22)
OUT_0: R0.1 (P0), U1.12 (P11)
OUT_1: R1.1 (P0), U1.13 (P12)
OUT_2: R2.1 (P0), U1.14 (P13)
OUT_3: R3.1 (P0), U1.15 (P14)
OUT_4: R4.1 (P0), U1.16 (P15)
OUT_5: R5.1 (P0), U1.17 (P16)
OUT_6: R6.1 (P0), U1.18 (P17)
OUT_7: R7.1 (P0), U1.19 (P18)
OUT_8: R8.1 (P0), U2.12 (P11)
OUT_9: R9.1 (P0), U2.13 (P12)
OUT_10: R10.1 (P0), U2.14 (P13)
OUT_11: R11.1 (P0), U2.15 (P14)
OUT_12: R12.1 (P0), U2.16 (P15)
OUT_13: R13.1 (P0), U2.17 (P16)
OUT_14: R14.1 (P0), U2.18 (P17)
OUT_15: R15.1 (P0), U2.19 (P18)
OUT_16: R16.1 (P0), U3.12 (P11)
OUT_17: R17.1 (P0), U3.13 (P12)
OUT_18: R18.1 (P0), U3.14 (P13)
OUT_19: R19.1 (P0), U3.15 (P14)
OUT_20: R20.1 (P0), U3.16 (P15)
OUT_21: R21.1 (P0), U3.17 (P16)
OUT_22: R22.1 (P0), U3.18 (P17)
OUT_23: R23.1 (P0), U3.19 (P18)
P3V3: C2.1 (P0), C4.1 (P0), C6.1 (P0), ISO1.1 (P0), ISO1.3 (P2), ISO2.1 (P0), ISO2.3 (P2), ISO3.1 (P0), ISO3.3 (P2), ISO4.1 (P0), ISO4.3 (P2), ISO5.1 (P0), ISO5.3 (P2), ISO6.1 (P0), ISO6.3 (P2), ISO7.1 (P0), ISO7.3 (P2), J4.3 (P2), J_STACK.7 (P6), J_STACK.19 (P18), U1.2 (P1), U2.2 (P1), U3.2 (P1), U4.1 (P0); also elsewhere on the board
P5V: J4.4 (P3), J_STACK.5 (P4), J_STACK.21 (P20); also elsewhere on the board
SCLK_P: ISO7.9 (P8), U1.22 (P21), U2.22 (P21), U3.22 (P21)
SDI_P: ISO7.10 (P9), U1.20 (P19)
SDO_P: ISO7.8 (P7), U3.21 (P20)
TRIGIN_0: ISO1.5 (P4), U4.7 (P6)
TRIGIN_1: ISO1.6 (P5), U4.8 (P7)
TRIGIN_2: ISO1.7 (P6), U4.9 (P8)
TRIGIN_3: ISO1.8 (P7), U4.10 (P9)
TRIGIN_4: ISO2.5 (P4), U4.11 (P10)
TRIGIN_5: ISO2.6 (P5), U4.12 (P11)
TRIGIN_6: ISO2.7 (P6), U4.13 (P12)
TRIGIN_7: ISO2.8 (P7), U4.14 (P13)
TRIGIN_8: ISO3.5 (P4), U4.15 (P14)
TRIGIN_9: ISO3.6 (P5), U4.16 (P15)
TRIGIN_10: ISO3.7 (P6), U4.17 (P16)
TRIGIN_11: ISO3.8 (P7), U4.18 (P17)
TRIGIN_12: ISO4.5 (P4), U4.19 (P18)
TRIGIN_13: ISO4.6 (P5), U4.20 (P19)
TRIGIN_14: ISO4.7 (P6), U4.21 (P20)
TRIGIN_15: ISO4.8 (P7), U4.22 (P21)
TRIGIN_16: ISO5.5 (P4), U4.23 (P22)
TRIGIN_17: ISO5.6 (P5), U4.24 (P23)
TRIGIN_18: ISO5.7 (P6), U4.25 (P24)
TRIGIN_19: ISO5.8 (P7), U4.26 (P25)
TRIGIN_20: ISO6.5 (P4), U4.27 (P26)
TRIGIN_21: ISO6.6 (P5), U4.28 (P27)
TRIGIN_22: ISO6.7 (P6), U4.29 (P28)
TRIGIN_23: ISO6.8 (P7), U4.30 (P29)
TRIG_0: ISO1.9 (P8), U1.4 (P3)
TRIG_1: ISO1.10 (P9), U1.5 (P4)
TRIG_2: ISO1.11 (P10), U1.6 (P5)
TRIG_3: ISO1.12 (P11), U1.7 (P6)
TRIG_4: ISO2.9 (P8), U1.8 (P7)
TRIG_5: ISO2.10 (P9), U1.9 (P8)
TRIG_6: ISO2.11 (P10), U1.10 (P9)
TRIG_7: ISO2.12 (P11), U1.11 (P10)
TRIG_8: ISO3.9 (P8), U2.4 (P3)
TRIG_9: ISO3.10 (P9), U2.5 (P4)
TRIG_10: ISO3.11 (P10), U2.6 (P5)
TRIG_11: ISO3.12 (P11), U2.7 (P6)
TRIG_12: ISO4.9 (P8), U2.8 (P7)
TRIG_13: ISO4.10 (P9), U2.9 (P8)
TRIG_14: ISO4.11 (P10), U2.10 (P9)
TRIG_15: ISO4.12 (P11), U2.11 (P10)
TRIG_16: ISO5.9 (P8), U3.4 (P3)
TRIG_17: ISO5.10 (P9), U3.5 (P4)
TRIG_18: ISO5.11 (P10), U3.6 (P5)
TRIG_19: ISO5.12 (P11), U3.7 (P6)
TRIG_20: ISO6.9 (P8), U3.8 (P7)
TRIG_21: ISO6.10 (P9), U3.9 (P8)
TRIG_22: ISO6.11 (P10), U3.10 (P9)
TRIG_23: ISO6.12 (P11), U3.11 (P10)
TX_0: J3.1 (P0), R0.2 (P1); also elsewhere on the board
TX_1: J3.2 (P1), R1.2 (P1); also elsewhere on the board
TX_2: J3.4 (P3), R2.2 (P1); also elsewhere on the board
TX_3: J3.5 (P4), R3.2 (P1); also elsewhere on the board
TX_4: J3.6 (P5), R4.2 (P1); also elsewhere on the board
TX_5: J3.7 (P6), R5.2 (P1); also elsewhere on the board
TX_6: J3.8 (P7), R6.2 (P1); also elsewhere on the board
TX_7: J3.9 (P8), R7.2 (P1); also elsewhere on the board
TX_8: J3.10 (P9), R8.2 (P1); also elsewhere on the board
TX_9: J3.11 (P10), R9.2 (P1); also elsewhere on the board
TX_10: J3.12 (P11), R10.2 (P1); also elsewhere on the board
TX_11: J3.13 (P12), R11.2 (P1); also elsewhere on the board
TX_12: J3.25 (P24), R12.2 (P1); also elsewhere on the board
TX_13: J3.14 (P13), R13.2 (P1); also elsewhere on the board
TX_14: J3.15 (P14), R14.2 (P1); also elsewhere on the board
TX_15: J3.16 (P15), R15.2 (P1); also elsewhere on the board
TX_16: J3.17 (P16), R16.2 (P1); also elsewhere on the board
TX_17: J3.18 (P17), R17.2 (P1); also elsewhere on the board
TX_18: J3.19 (P18), R18.2 (P1); also elsewhere on the board
TX_19: J3.20 (P19), R19.2 (P1); also elsewhere on the board
TX_20: J3.21 (P20), R20.2 (P1); also elsewhere on the board
TX_21: J3.22 (P21), R21.2 (P1); also elsewhere on the board
TX_22: J3.23 (P22), R22.2 (P1); also elsewhere on the board
TX_23: J3.24 (P23), R23.2 (P1); also elsewhere on the board
VPP: C1.1 (P0), C3.1 (P0), C5.1 (P0), J4.1 (P0), J_STACK.1 (P0), J_STACK.3 (P2), J_STACK.23 (P22), U1.1 (P0), U2.1 (P0), U3.1 (P0); also elsewhere on the board

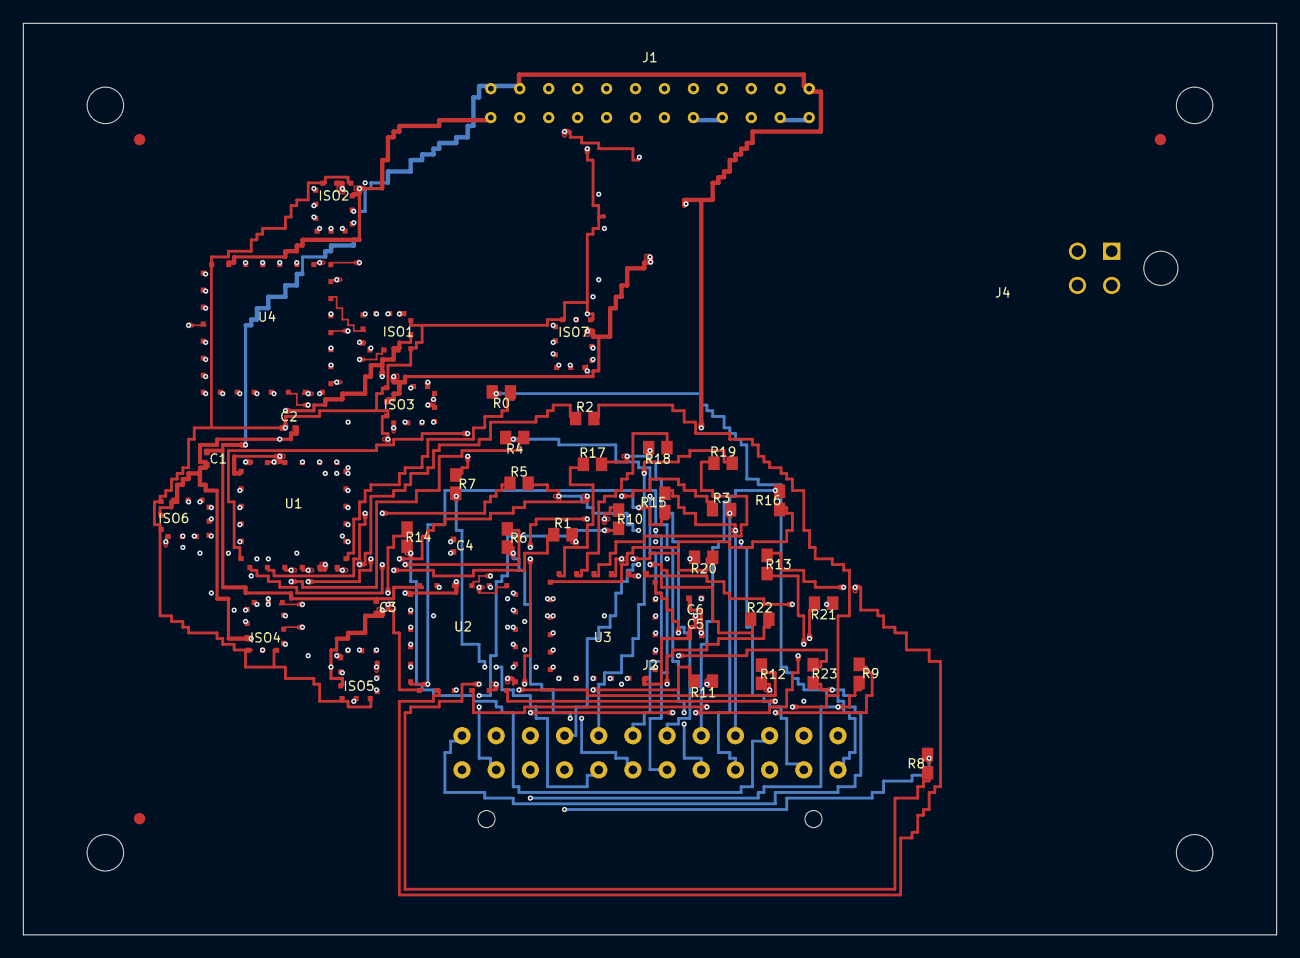
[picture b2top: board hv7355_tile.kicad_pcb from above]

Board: 6 copper layers, 110.0 x 80.0 mm, 51 parts (0 on the bottom side), 111 nets.

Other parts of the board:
FID: FIDUCIAL
FID#2, FID#3: FIDUCIAL
J1: J_STACK_Samtec_TSW-112-07-G-D
J2: MOLEX_430452400
MH: MountingHole
MH#2, MH#3, MH#4: MountingHole

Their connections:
BUS_CLK: J1.17; also elsewhere on the board
BUS_LATCH: J1.15; also elsewhere on the board
BUS_SCLK: J1.9; also elsewhere on the board
BUS_SDI: J1.11; also elsewhere on the board
BUS_SDO: J1.13; also elsewhere on the board
GND: J1.2, J1.4, J1.6, J1.8, J1.10, J1.12, J1.14, J1.16, J1.18, J1.20, J1.22, J1.24; also elsewhere on the board
P3V3: J1.7, J1.19; also elsewhere on the board
P5V: J1.5, J1.21; also elsewhere on the board
TX_0: J2.1; also elsewhere on the board
TX_1: J2.2; also elsewhere on the board
TX_2: J2.3; also elsewhere on the board
TX_3: J2.4; also elsewhere on the board
TX_4: J2.5; also elsewhere on the board
TX_5: J2.6; also elsewhere on the board
TX_6: J2.7; also elsewhere on the board
TX_7: J2.8; also elsewhere on the board
TX_8: J2.9; also elsewhere on the board
TX_9: J2.10; also elsewhere on the board
TX_10: J2.11; also elsewhere on the board
TX_11: J2.12; also elsewhere on the board
TX_12: J2.13; also elsewhere on the board
TX_13: J2.14; also elsewhere on the board
TX_14: J2.15; also elsewhere on the board
TX_15: J2.16; also elsewhere on the board
TX_16: J2.17; also elsewhere on the board
TX_17: J2.18; also elsewhere on the board
TX_18: J2.19; also elsewhere on the board
TX_19: J2.20; also elsewhere on the board
TX_20: J2.21; also elsewhere on the board
TX_21: J2.22; also elsewhere on the board
TX_22: J2.23; also elsewhere on the board
TX_23: J2.24; also elsewhere on the board
VPP: J1.1, J1.3, J1.23; also elsewhere on the board
